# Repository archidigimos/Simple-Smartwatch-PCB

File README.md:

# Simple-Smartwatch-PCB
Capable of measuring heart rate and other vital parameters. LCD not attached.

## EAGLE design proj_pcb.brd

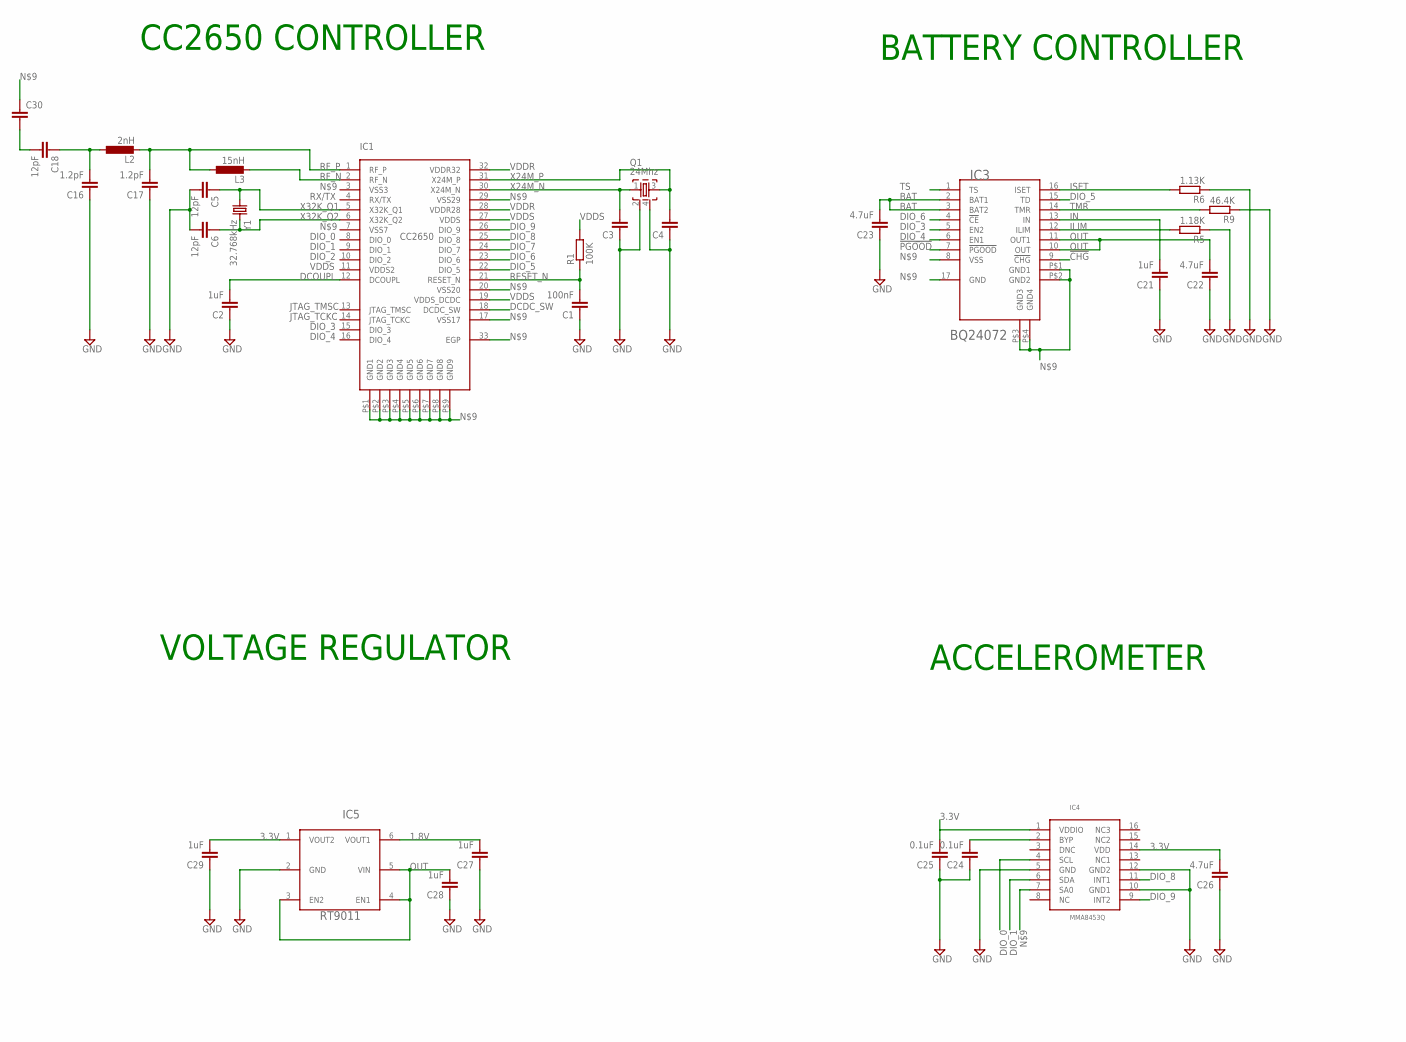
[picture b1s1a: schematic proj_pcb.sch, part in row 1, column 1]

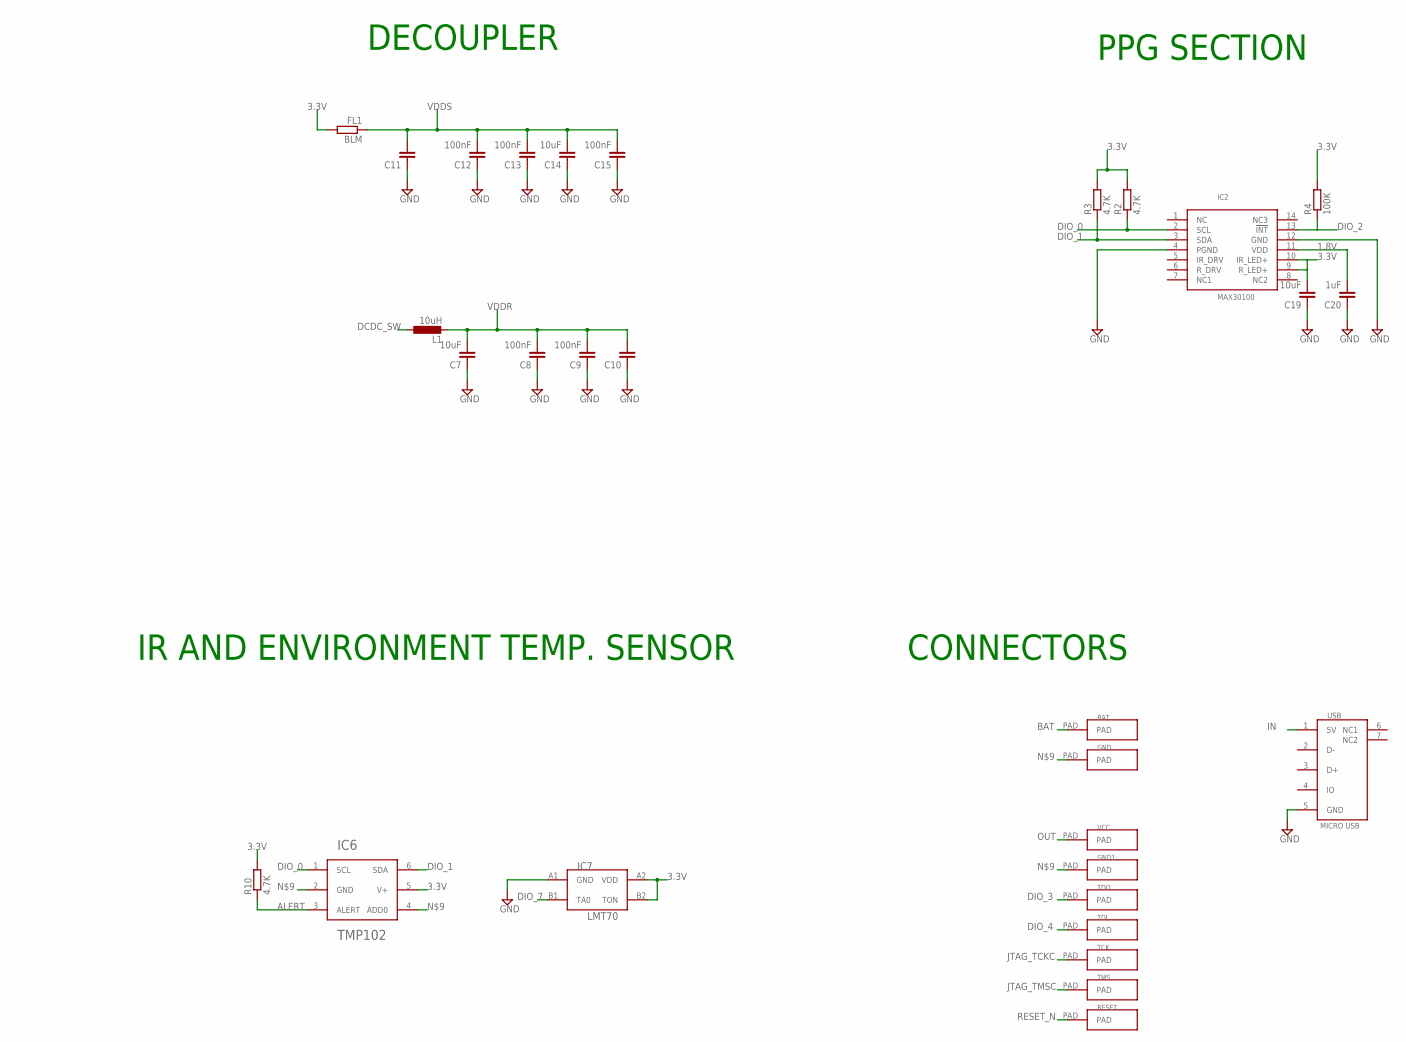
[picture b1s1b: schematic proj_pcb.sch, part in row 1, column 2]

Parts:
BAT: SMD_PAD
BLM: FL1; R0603
C1, C8, C9, C12, C13, C15: 100nF; C0603
C2, C20, C21, C27, C28, C29: 1uF; C0603
C3, C4, C10, C11: C-EUC0603; C0603
C5, C6, C18: 12pF; C0603
C7, C14, C19: 10uF; C0603
C16, C17: 1.2pF; C0603
C22, C23, C26: 4.7uF; C0603
C24, C25: 0.1uF; C0603
C30: C-EUC1808; C1808
GND, GND1: SMD_PAD
IC1: CC2650_UC
IC2: MAX30100
IC3: BQ24072_BATTERY
IC4: MMA8453Q
IC5: RT9011
IC6: TMP102
IC7: LMT70
L1: 10uH; L2012C
L2: 2nH; L2012C
L3: 15nH; L2012C
Q1: 24Mhz; FA-128
R1, R4: 100K; R0603
R2, R3, R10: 4.7K; R0603
R5: 1.18K; R0603
R6: 1.13K; R0603
R9: 46.4K; R0603
RESET: SMD_PAD
TCK: SMD_PAD
TDI: SMD_PAD
TDO: SMD_PAD
TMS: SMD_PAD
USB: MICRO_USB
VCC: SMD_PAD
Y1: 32.768kHz; FC-12M

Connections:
1.8V: C20.2, C27.2, IC2.11 (VDD), IC5.6 (VOUT1)
3.3V: BLM.2, C19.2, C25.2, C26.2, C29.2, IC2.9 (R_LED+), IC2.10 (IR_LED+), IC4.1 (VDDIO), IC4.14 (VDD), IC5.1 (VOUT2), IC6.5 (V+), IC7.A2 (VDD), IC7.B2 (TON), R2.2, R3.2, R4.2, R10.2
!CHG: IC3.9 (!CHG)
!PGOOD: IC3.7 (!PGOOD)
ALERT: IC6.3 (ALERT), R10.1
BAT: BAT.PAD, C23.2, IC3.2 (BAT1), IC3.3 (BAT2)
DCDC_SW: IC1.18 (DCDC_SW), L1.1
DCOUPL: C2.2, IC1.12 (DCOUPL)
DIO_0: IC1.8 (DIO_0), IC2.2 (SCL), IC4.4 (SCL), IC6.1 (SCL), R2.1
DIO_1: IC1.9 (DIO_1), IC2.3 (SDA), IC4.6 (SDA), IC6.6 (SDA), R3.1
DIO_2: IC1.10 (DIO_2), IC2.13 (!INT), R4.1
DIO_3: IC1.15 (DIO_3), IC3.5 (EN2), TDO.PAD
DIO_4: IC1.16 (DIO_4), IC3.6 (EN1), TDI.PAD
DIO_5: IC1.22 (DIO_5), IC3.15 (TD)
DIO_6: IC1.23 (DIO_6), IC3.4 (!CE)
DIO_7: IC1.24 (DIO_7), IC7.B1 (TA0)
DIO_8: IC1.25 (DIO_8), IC4.11 (INT1)
DIO_9: IC1.26 (DIO_9), IC4.9 (INT2)
ILIM: IC3.12 (ILIM), R5.2
IN: C21.2, IC3.13 (IN), USB.1 (5V)
ISET: IC3.16 (ISET), R6.2
JTAG_TCKC: IC1.14 (JTAG_TCKC), TCK.PAD
JTAG_TMSC: IC1.13 (JTAG_TMSC), TMS.PAD
unnamed: C16.2, C18.1, L2.1
unnamed: C18.2, C30.2
unnamed: C24.2, IC4.2 (BYP)
unnamed: C1.1, C2.1, C3.1, C4.1, C5.2, C6.2, C7.1, C8.1, C9.1, C10.1, C11.1, C12.1, C13.1, C14.1, C15.1, C16.1, C17.1, C19.1, C20.1, C21.1, C22.1, C23.1, C24.1, C25.1, C26.1, C27.1, C28.1, C29.1, C30.1, GND.PAD, GND1.PAD, IC1.3 (VSS3), IC1.7 (VSS7), IC1.17 (VSS17), IC1.20 (VSS20), IC1.29 (VSS29), IC1.33 (EGP), IC1.P$1 (GND1), IC1.P$2 (GND2), IC1.P$3 (GND3), IC1.P$4 (GND4), IC1.P$5 (GND5), IC1.P$6 (GND6), IC1.P$7 (GND7), IC1.P$8 (GND8), IC1.P$9 (GND9), IC2.4 (PGND), IC2.12 (GND), IC3.8 (VSS), IC3.17 (GND), IC3.P$1 (GND1), IC3.P$2 (GND2), IC3.P$3 (GND3), IC3.P$4 (GND4), IC4.5 (GND), IC4.7 (SA0), IC4.10 (GND1), IC4.12 (GND2), IC5.2 (GND), IC6.2 (GND), IC6.4 (ADD0), IC7.A1 (GND), Q1.2, Q1.4, R5.1, R6.1, R9.1, USB.5 (GND)
OUT: C22.2, C28.2, IC3.10 (OUT), IC3.11 (OUT1), IC5.3 (EN2), IC5.4 (EN1), IC5.5 (VIN), VCC.PAD
RESET_N: C1.2, IC1.21 (RESET_N), R1.1, RESET.PAD
RF_N: IC1.2 (RF_N), L3.2
RF_P: C17.2, IC1.1 (RF_P), L2.2, L3.1
RX/TX: IC1.4 (RX/TX)
TMR: IC3.14 (TMR), R9.2
TS: IC3.1 (TS)
VDDR: C7.2, C8.2, C9.2, C10.2, IC1.28 (VDDR28), IC1.32 (VDDR32), L1.2
VDDS: BLM.1, C11.2, C12.2, C13.2, C14.2, C15.2, IC1.11 (VDDS2), IC1.19 (VDDS_DCDC), IC1.27 (VDDS), R1.2
X24M_N: C3.2, IC1.30 (X24M_N), Q1.1
X24M_P: C4.2, IC1.31 (X24M_P), Q1.3
X32K_Q1: C5.1, IC1.5 (X32K_Q1), Y1.1
X32K_Q2: C6.1, IC1.6 (X32K_Q2), Y1.2

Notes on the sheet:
CC2650 CONTROLLER
BATTERY CONTROLLER
DECOUPLER
PPG SECTION
VOLTAGE REGULATOR
ACCELEROMETER
IR AND ENVIRONMENT TEMP. SENSOR
CONNECTORS

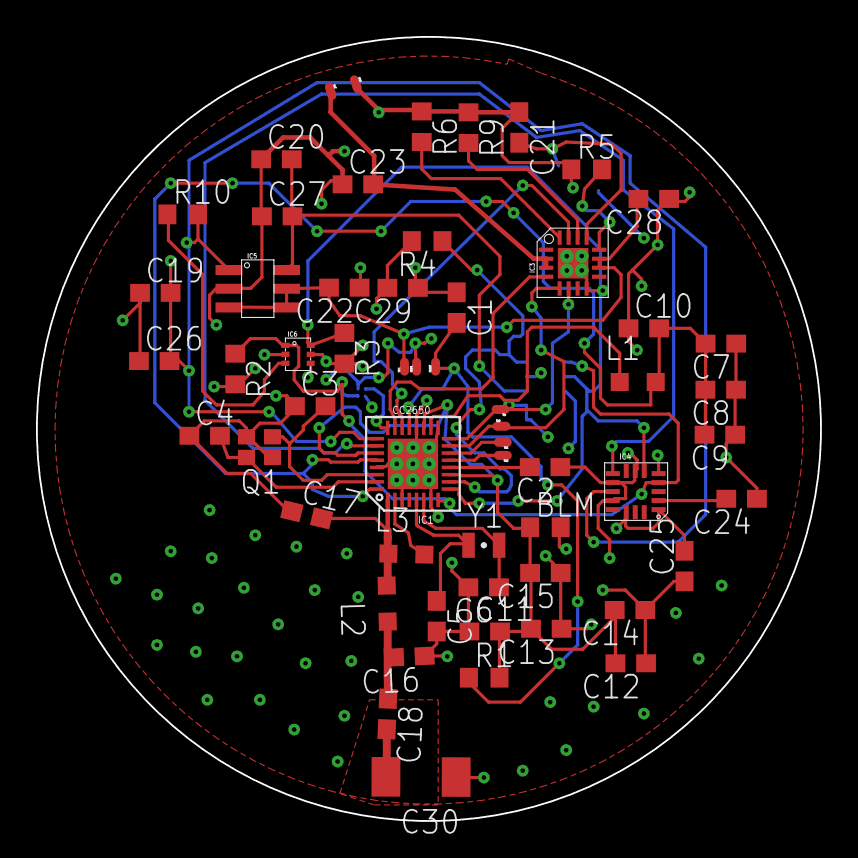
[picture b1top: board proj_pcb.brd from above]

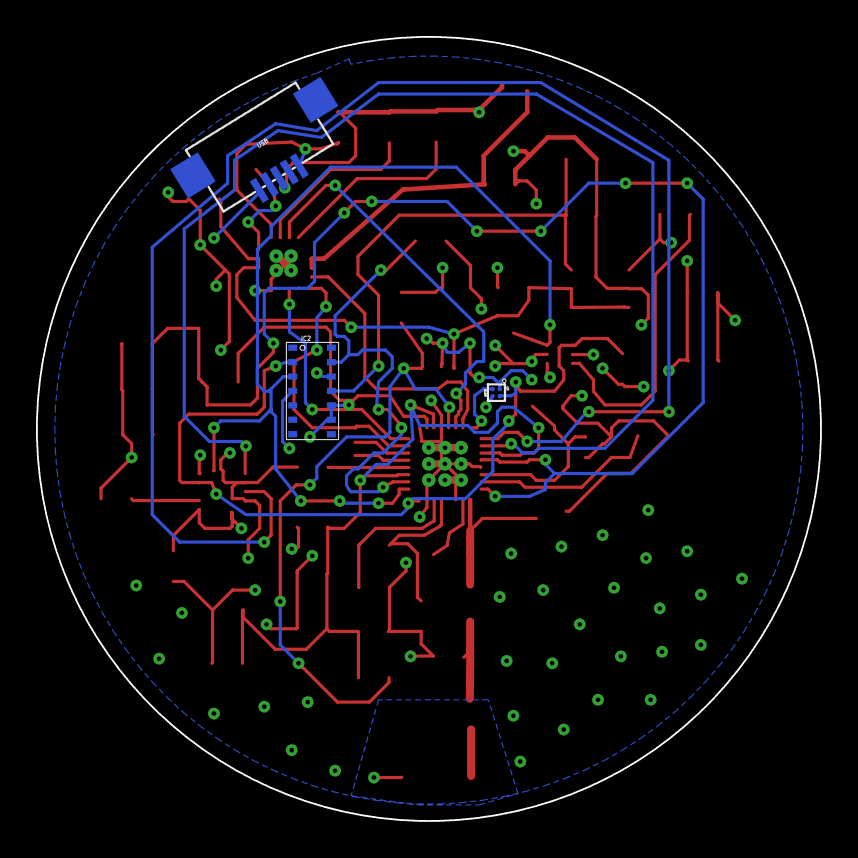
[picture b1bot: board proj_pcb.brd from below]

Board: 4 copper layers, 43.6 x 43.6 mm, 61 parts (3 on the bottom side), 36 nets.

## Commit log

2017-08-08 :circus_tent: Added .gitattributes & .gitignore files
2017-08-08 Screenshot
